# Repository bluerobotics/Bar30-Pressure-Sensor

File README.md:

# Bar30 Pressure Sensor

Arduino software library is available [here](http://github.com/bluerobotics/BlueRobotics_MS5837_Library/).

The schematic and board layout are designed in EagleCAD.

# Hardware

## Description

The Bar30 pressure sensor is a high-pressure, high-resolution pressure sensor that is sealed from the water and ready to install in a watertight enclosure. With 0.2 bar resolution, it has an amazing depth measurement resolution of 2mm in the water column!

The sensor is the Measurement Specialties MS5837-30BA, which can measure up to 30 bar (300m depth) and communicates over I2C. It comes standard with a 4-pin DF13 connector and compatible with most DroneCode compatible boards including the APM2.6, PixHawk, and others.

## Features

* Measure up to 300m water depth with 2mm resolution
* Reverse polarity protection
* Standard DF13 connector for connection to DroneCode boards such as APM, PixHawk, Navio2, etc.
* Sealed in a bulkhead penetrator for easy installation into any 10mm hole

## Compatibility

The Bar30 sensor is compatible with any device with 3.3V I<sup>2</sup>C logic. When using with a 5V device, such as an Arduino Uno, it is necessary to use a logic level converter.

##Configuration

--

##Ratings

**Electrical:**

| **Item** | **Condition** | **Value** |
| -------------: | :---------: | --- |
| Supply Voltage| - | 2.5-5.5 volts |
| I<sup>2</sup>C Logic Voltage | - | 2.5-3.6 volts |
| Peak Current   | - | 1.25 mA   |

**Pressure:**

| **Item** | **Condition** | **Value** |
| -------------: | :---------: | --- |
| Maximum Mechanical Pressure | - | 50 bar |
|Operating Pressure| - |0-30 bar [up to 1000 ft (300 m) in water]|
|Absolute Accuracy  (0-40&deg;C) | From 0-6 bar | +/- 50 mbar 	(51 cm in freshwater)		 |
|  				   | From 0-20 bar | +/- 100 mbar (102 cm in freshwater)			 |
|				   | From 0-30 bar | +/- 200 mbar (204 cm in freshwater)    	 |
|Absolute Accuracy (-25-85&deg;C)| From 0-6 bar | +/- 100 mbar 	(102 cm in freshwater)		 |
|  				   | From 0-20 bar | +/- 200 mbar (204 cm in freshwater)			 |
|				   | From 0-30 bar | +/- 400 mbar (408 cm in freshwater)     	 |

**Temperature:**

| **Item** | **Condition** | **Value** |
| -------------: | :---------: | --- |
| Operating Temperature | - | -20 to +85&deg;C |
| Storage Temperature | - | -40 to +85&deg;C                        |
| Absolute Accuracy   | From 0-10 bar at 0-60&deg;C | +/- 1.5&deg;C      |
|                     | From 0-30 bar at -20-85&deg;C |  +/- 4.0&deg;C   |

**Physical:**

| **Item** | **Value** |
| -------------: | ------------- |
| Wire Colors | Green - I<sup>2</sup>C Clock (SCL) |
|             | White - I<sup>2</sup>C Data (SDA)  |
|             | Red - Positive (2.5-5.5V) |
|             | Black - Ground          |
| Overall Length | 37 mm |
| Thread Size    | M10x1.5 20 mm threaded |
| Recommended Through Hole Size | 10-11 mm |
| Wrench Flats | 16 mm |

##Example Setups

Examples TBD

##Physical Specifications

* Bulkhead hole size: 10-10.5mm
* Wire length: 11" (280mm)

##License

The Bar30 Pressure Sensor Hardware Design is released under the MIT License.

##Revision History

0.0 - Under development

0.1 - First production version (marked with rev4)

0.2 - Minor layout changes (marked with rev5)

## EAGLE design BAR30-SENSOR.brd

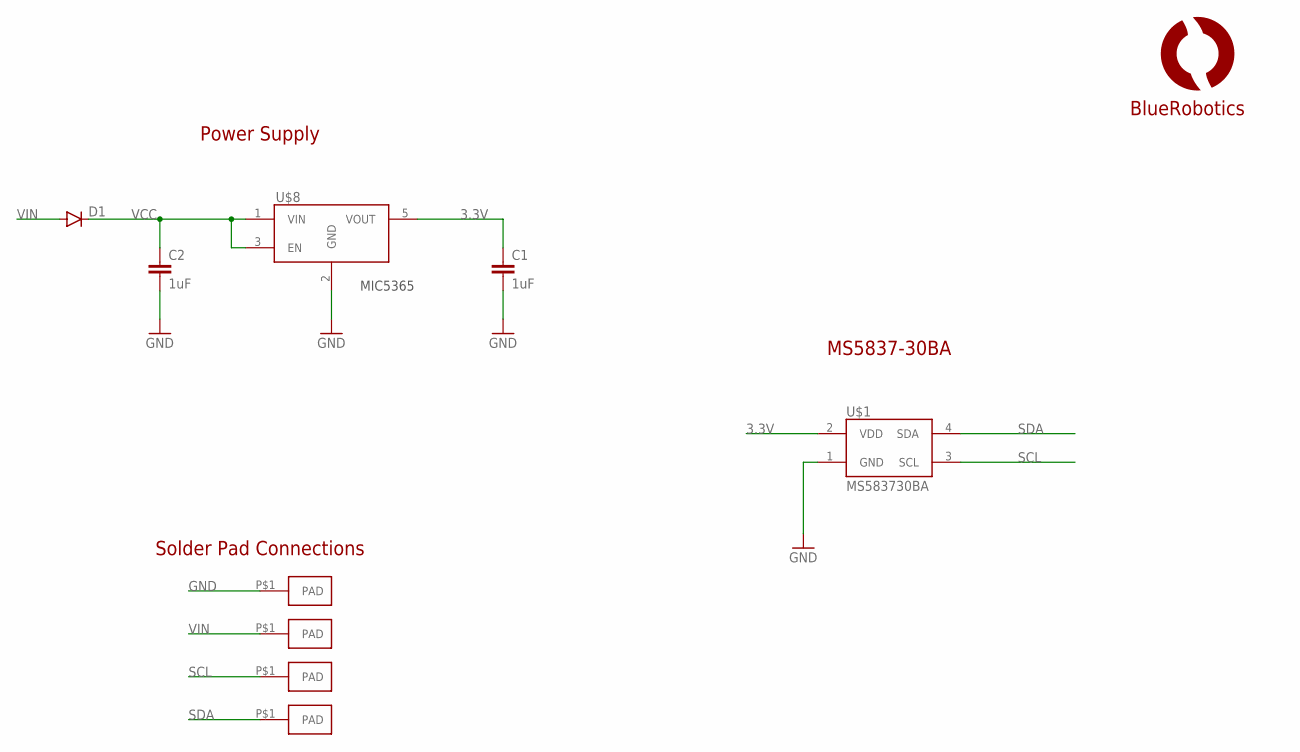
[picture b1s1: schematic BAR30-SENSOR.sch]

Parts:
C1, C2: 1uF; C0402
D1: DIODESOD523; SOD523
U$1: MS583730BA; MS5837
U$3, U$4, U$5, U$6: PAD1.5X3MM; PAD-1.5X3MM
U$7: LOGOBR-LOGO-S; BR-LOGO-SMALL
U$8: VREG-MIC5365; SC70-5L

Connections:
3.3V: C1.1, U$1.2 (VDD), U$8.5 (VOUT)
GND: C1.2, C2.2, U$1.1 (GND), U$3.P$1, U$8.2 (GND)
SCL: U$1.3 (SCL), U$5.P$1
SDA: U$1.4 (SDA), U$6.P$1
VCC: C2.1, D1.C, U$8.1 (VIN), U$8.3 (EN)
VIN: D1.A, U$4.P$1

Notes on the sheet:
Solder Pad Connections
MS5837-30BA
Power Supply
MIC5365

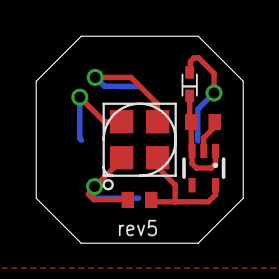
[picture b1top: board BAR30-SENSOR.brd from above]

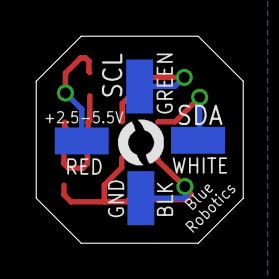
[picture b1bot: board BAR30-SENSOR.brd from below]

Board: 2 copper layers, 11.5 x 11.5 mm, 10 parts (5 on the bottom side), 6 nets.

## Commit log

2015-10-21 Initial commit with board files, DXF script, and README
2015-11-02 Updated frame.
2015-11-03 Change voltage regulator from zener to LDO.
2015-11-16 Fixed incorrect regulator footprint.
2015-12-22 Added a ground via and change silk screen on bottom to reflect proper voltage range.
2015-12-22 A few minor aesthetic changes. Ordering this version.
2016-01-10 Added PDF schematic, updated readme.
2016-01-18 Last minute major redesign for DroneCode I2C compatibility.
    PixHawk and others cannot handle 5V I2C logic but have 5V I2C power supplies!
2016-01-24 README: Updates for most recent revision
2016-01-24 README: Removed logic level note
2016-01-26 Fix README format issues.

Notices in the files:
parts and their libraries:
SparkFun-DiscreteSemi: Licensing: Creative Commons ShareAlike 4.0 International - https://creativecommons.org/licenses/by-sa/4.0
